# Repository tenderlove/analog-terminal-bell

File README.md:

# Analog Terminal Bell

Welcome to the Analog Terminal Bell!

The Analog Terminal Bell is a bell that rings any time a bell character is
displayed on your terminal.  Simply plug the bell in to USB and enable "Analog
Bell" in your terminal settings.

Never miss a terminal bell notification again!

Here is a photo of the bell:

Here is a video explanation:

## Actual Product Details

This bell is not actually for sale.  You have to build it yourself!  This
project uses an MCP2221A microchip to drive a solenoid and hit a bell.

### Electronic Hardware

Information about the electronic hardware to build this project can be found in
the `pcb` folder.  Just check out the [README](pcb/README.md) there for details
on how to build the electronic hardware for this project.

I used through hole components on the PCB to make assembly as easy as possible.

### Physical Hardware

The bell can be found at many stores like [amazon](https://www.amzn.com/s?k=bell) or [staples](https://www.staples.com/call+bell/directory_call%2520bell)

### Software

Unlike an Arduino, this microchip doesn't need any firmware, we can control it
via USB HID.  See the [README](software/README.md) in the `software` folder for
details on how to control the bell from your computer.

Note that if you want iTerm2 to ring the bell like in the commercial, you'll
need a custom build of iTerm2.  You can find the patches for iTerm2
[here](https://github.com/tenderlove/iTerm2/tree/analog-terminal-bell).

### Case and Mounting

The case is 3D printed and the stl files can be found in the [case](case) folder.

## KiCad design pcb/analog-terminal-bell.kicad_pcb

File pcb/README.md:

# Analog Terminal Bell PCB

This directory contains the PCB design for the analog terminal bell.

## PCB

The PCB is designed using KiCad.  If you don't want to deal with KiCad, it's no
problem.  Just upload the `gerbers.zip` file to any PCB manufacturer and you
should be on your way!

## Components

Here are the components needed:

* [Mini USB B Connector](https://www.digikey.com/product-detail/en/molex/0548190519/WM17115-ND/773802) ($1.72)
* [10k resistor](https://www.digikey.com/product-detail/en/stackpole-electronics-inc/CF14JT10K0/CF14JT10K0CT-ND/1830374) ($0.10)
* [1k resistor](https://www.digikey.com/product-detail/en/stackpole-electronics-inc/CF14JT1K00/CF14JT1K00CT-ND/1830350) ($0.10)
* [47nf capacitor](https://www.digikey.com/product-detail/en/vishay-beyschlag-draloric-bc-components/K473K15X7RF5TH5/BC1099CT-ND/286721) ($0.22)
* [1N4004 diode](https://www.digikey.com/product-detail/en/micro-commercial-co/1N4004-TP/1N4004-TPMSCT-ND/773691) ($0.12)
* [TIP 122 or 102](https://www.digikey.com/product-detail/en/stmicroelectronics/TIP102/497-2546-5-ND/603571) ($0.70)
* [Solenoid](https://www.digikey.com/product-detail/en/sparkfun-electronics/ROB-11015/1568-1592-ND/6163694) ($4.95)
* [MCP2221a](https://www.digikey.com/product-detail/en/microchip-technology/MCP2221A-I-P/MCP2221A-I-P-ND/6009296) ($2.27)
* [JST connector](https://www.digikey.com/short/zfj702) ($0.17)
* [14 Pin Socket](https://www.digikey.com/product-detail/en/on-shore-technology-inc/ED14DT/ED3045-5-ND/4147595) ($0.18)

* [Bell](https://www.amazon.com/gp/product/B07816SJSB/) ($7.99)

The electronic components for this project should cost around $11 (before
shipping, taxes, etc).

## Assembly

All of the components go on top of the board, except the USB connector. The
USB connector goes on the bottom of the board!

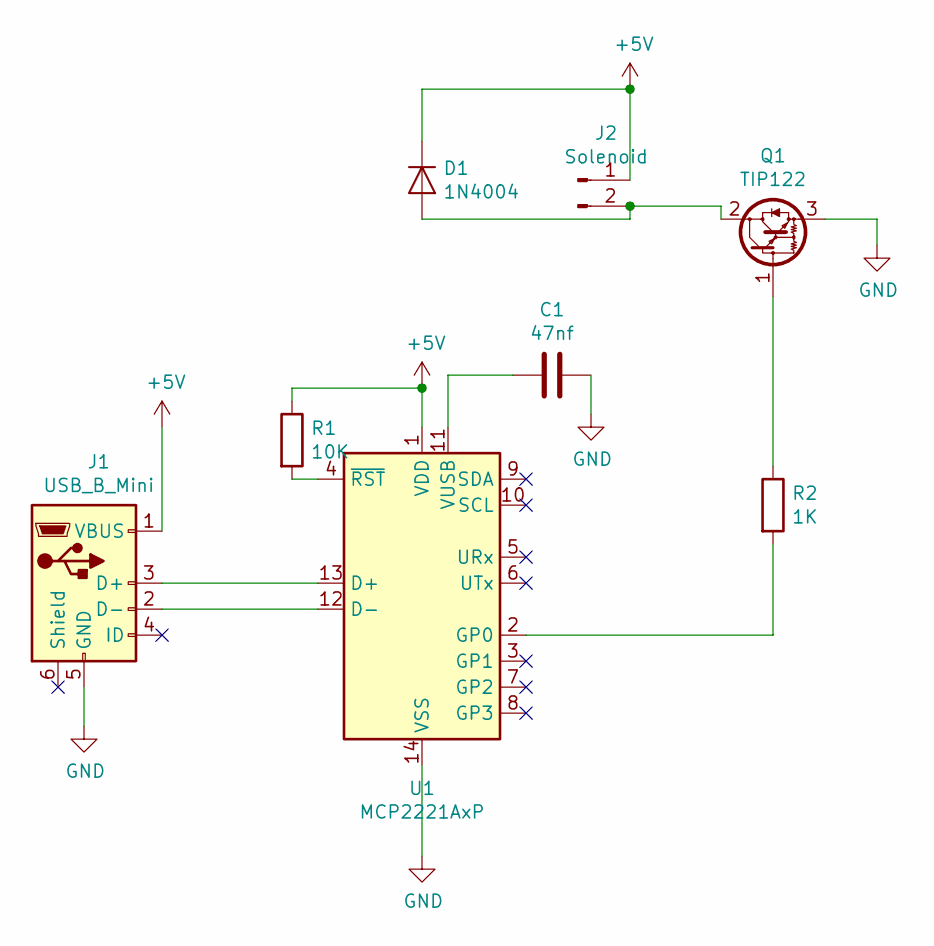
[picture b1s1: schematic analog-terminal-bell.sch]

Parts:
C1: 47nf; C_Disc_D4.7mm_W2.5mm_P5.00mm
D1: 1N4004; D_DO-41_SOD81_P10.16mm_Horizontal
J1: USB_B_Mini; USB_Mini_B_Female_548190519
J2: Solenoid; JST_PH_B2B-PH-K_1x02_P2.00mm_Vertical
Q1: TIP122; TO-220-3_Horizontal_TabDown
R1: 10K; R_Axial_DIN0207_L6.3mm_D2.5mm_P7.62mm_Horizontal
R2: 1K; R_Axial_DIN0207_L6.3mm_D2.5mm_P7.62mm_Horizontal
U1: MCP2221AxP; DIP-14_W7.62mm

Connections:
+5V: D1.1 (K), J1.1 (VBUS), J2.1, R1.1, U1.1 (VDD)
GND: C1.1, J1.5 (GND), Q1.3 (E), U1.14 (VSS)
unnamed: C1.2, U1.11 (VUSB)
unnamed: D1.2 (A), J2.2, Q1.2 (C)
unnamed: J1.2 (D-), U1.12 (D-)
unnamed: J1.3 (D+), U1.13 (D+)
unnamed: Q1.1 (B), R2.1
unnamed: R1.2, U1.4 (~RST)
unnamed: R2.2, U1.2 (GP0)

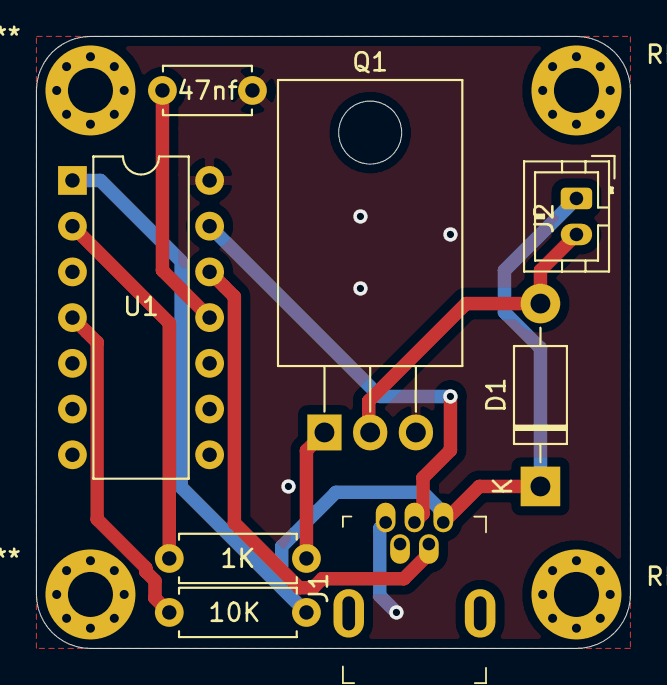
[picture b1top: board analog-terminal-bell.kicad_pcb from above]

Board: 2 copper layers, 33.0 x 34.0 mm, 8 parts (0 on the bottom side), 9 nets.

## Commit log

2020-08-16 base seems to be working
2020-08-21 current version
2020-08-22 Adding a solenoid mount design
2020-08-22 Make the solenoid mount file `use`able
2020-08-22 built the solenoid stand
2020-08-22 small refactor
2020-08-23 Make post go up
2020-08-23 This case seems to work well!
2020-08-30 update bottom text
2020-08-30 seems to be working
2020-08-30 adding pcb
2020-08-30 cleaning up case
2020-08-30 adding stl files for the case
2020-08-30 adding makefile
2020-08-30 more updates
2020-09-05 updating readme
2020-09-05 more readme updates
2020-09-08 Fix YouTube link
2020-09-08 Add License
    Forgot to add this, so here it is.
2020-09-10 Make YouTube link look clickable
2020-09-18 Added links to a bell that can be bought
2020-09-25 Fixing amazon bell link
    Changes the query from `terminal bell` to `bell`
2020-10-04 Sample C program using the cross-platform HIDAPI library.
2021-04-01 refactor case
